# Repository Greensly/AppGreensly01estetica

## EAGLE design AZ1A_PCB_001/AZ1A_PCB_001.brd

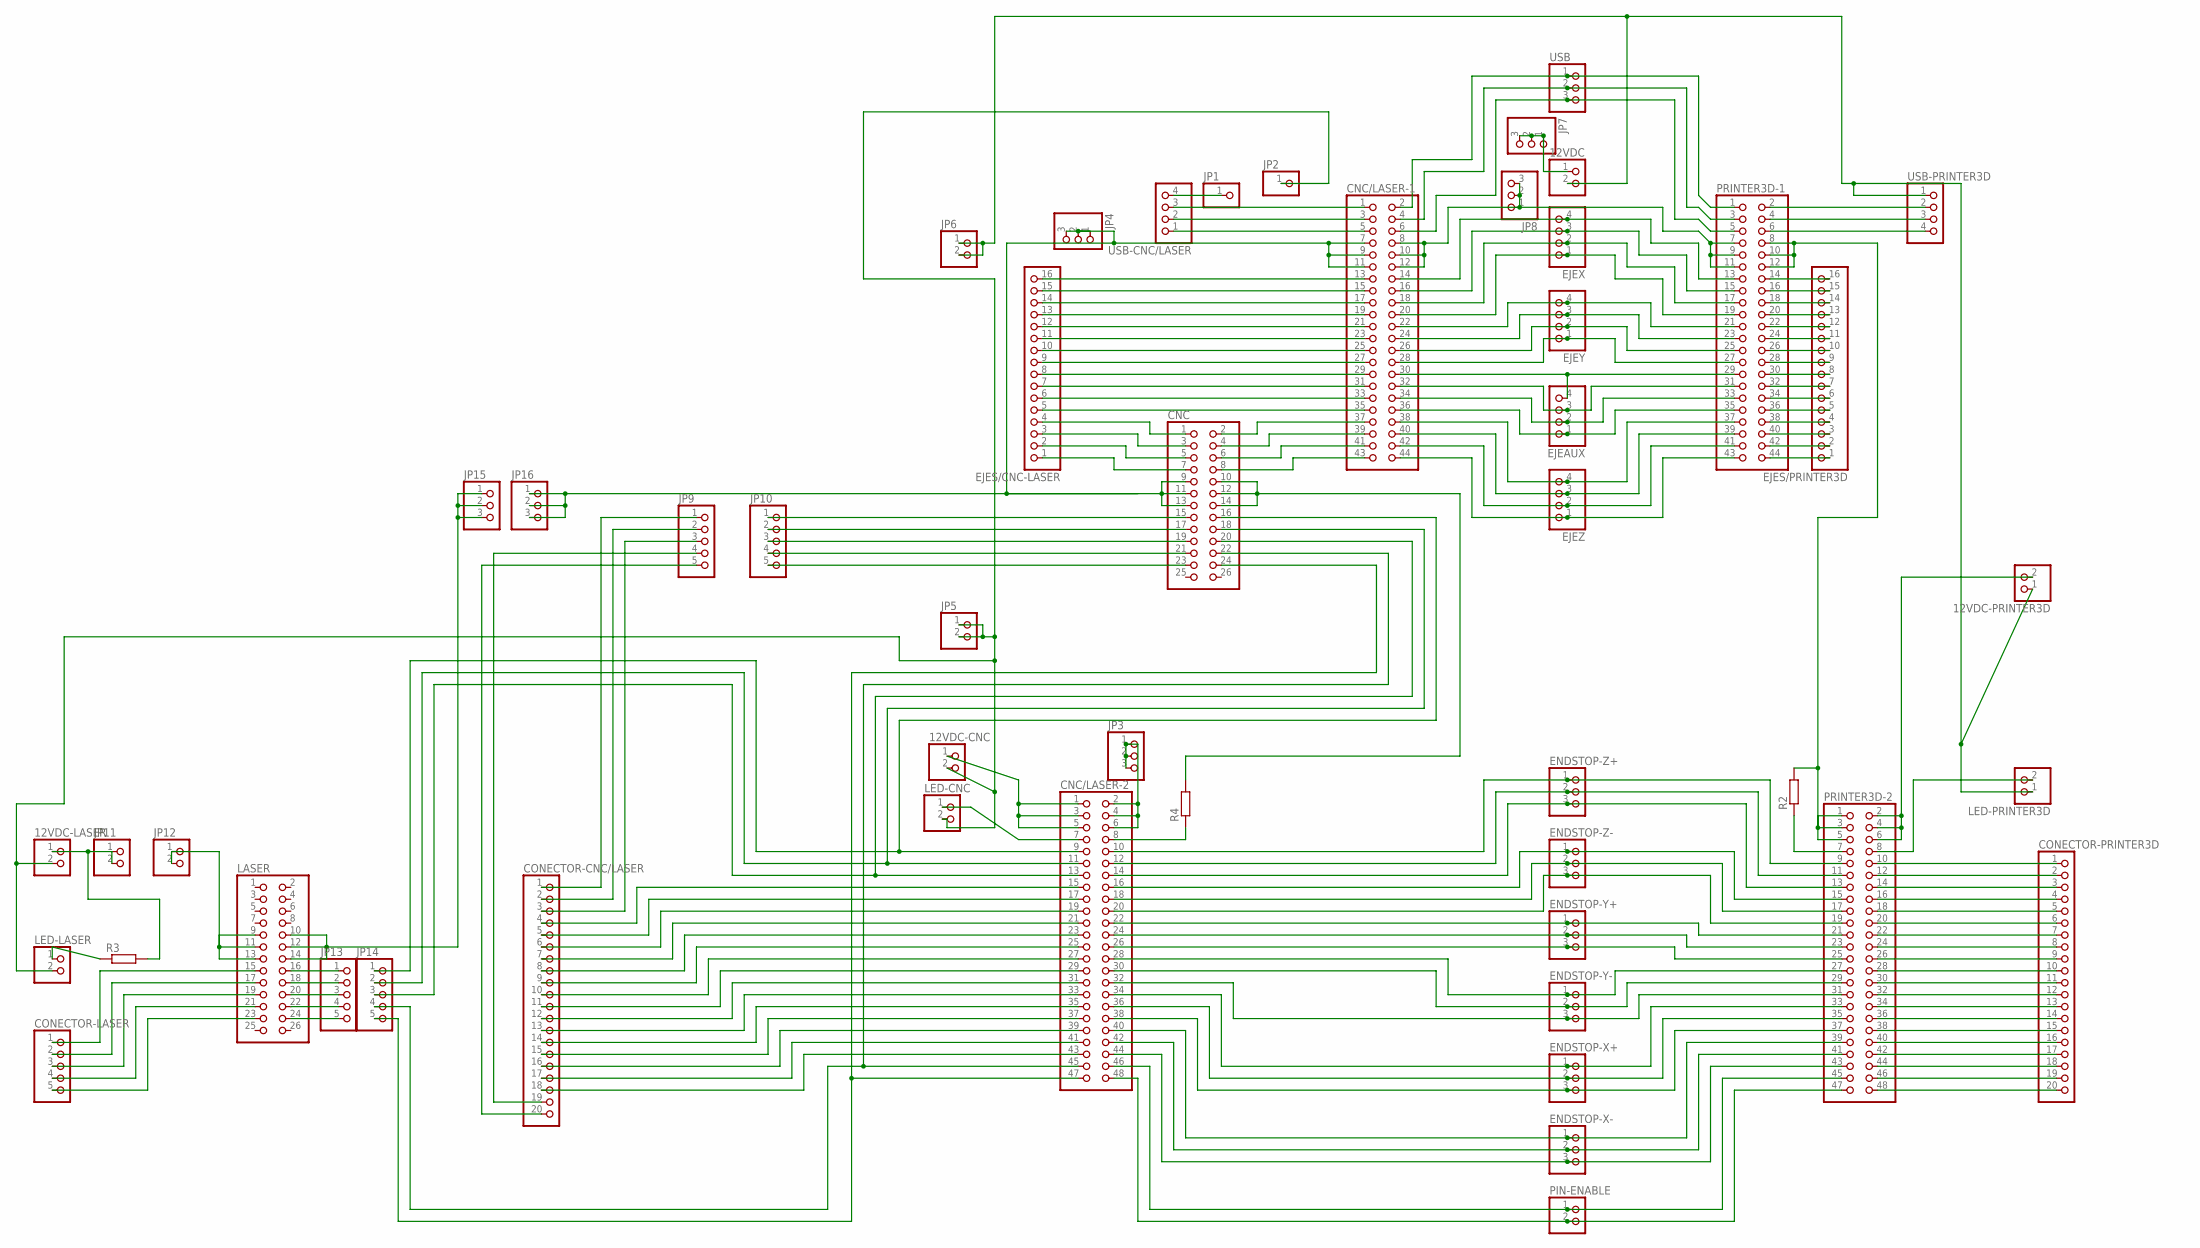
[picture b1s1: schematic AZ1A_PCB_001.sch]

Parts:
12VDC, 12VDC-CNC, 12VDC-LASER, 12VDC-PRINTER3D: PINHD-1X2; 1X02
CNC: PINHD-2X13; 2X13
CNC/LASER-1: PINHD-2X22; 2X22
CNC/LASER-2: PINHD-2X24; 2X24
CONECTOR-CNC/LASER: PINHD-1X20; 1X20
CONECTOR-LASER: PINHD-1X5; 1X05
CONECTOR-PRINTER3D: PINHD-1X20; 1X20
EJEAUX: PINHD-1X4; 1X04
EJES/CNC-LASER: PINHD-1X16; 1X16
EJES/PRINTER3D: PINHD-1X16; 1X16
EJEX: PINHD-1X4; 1X04
EJEY: PINHD-1X4; 1X04
EJEZ: PINHD-1X4; 1X04
ENDSTOP-X+: PINHD-1X3; 1X03
ENDSTOP-X-: PINHD-1X3; 1X03
ENDSTOP-Y+: PINHD-1X3; 1X03
ENDSTOP-Y-: PINHD-1X3; 1X03
ENDSTOP-Z+: PINHD-1X3; 1X03
ENDSTOP-Z-: PINHD-1X3; 1X03
JP1, JP2: PINHD-1X1; 1X01
JP3, JP4, JP7, JP8, JP15, JP16: PINHD-1X3; 1X03
JP5, JP6, JP11, JP12: PINHD-1X2; 1X02
JP9, JP10, JP13, JP14: PINHD-1X5; 1X05
LASER: PINHD-2X13; 2X13
LED-CNC: PINHD-1X2; 1X02
LED-LASER: PINHD-1X2; 1X02
LED-PRINTER3D: PINHD-1X2; 1X02
PIN-ENABLE: PINHD-1X2; 1X02
PRINTER3D-1: PINHD-2X22; 2X22
PRINTER3D-2: PINHD-2X24; 2X24
R2, R3, R4: R-EU_0204/5; 0204/5
USB: PINHD-1X3; 1X03
USB-CNC/LASER: PINHD-1X4; 1X04
USB-PRINTER3D: PINHD-1X4; 1X04

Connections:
unnamed: EJES/PRINTER3D.1, PRINTER3D-1.44
unnamed: CNC/LASER-1.16, EJEX.3, PRINTER3D-1.15
unnamed: CNC/LASER-1.18, EJEX.2, PRINTER3D-1.17
unnamed: CNC/LASER-1.20, EJEX.1, PRINTER3D-1.19
unnamed: CNC/LASER-1.22, EJEY.4, PRINTER3D-1.21
unnamed: CNC/LASER-1.24, EJEY.3, PRINTER3D-1.23
unnamed: CNC/LASER-1.26, EJEY.2, PRINTER3D-1.25
unnamed: CNC/LASER-1.28, EJEY.1, PRINTER3D-1.27
unnamed: CNC/LASER-1.30, EJEAUX.4, PRINTER3D-1.29
unnamed: CNC/LASER-1.32, EJEAUX.3, PRINTER3D-1.31
unnamed: CNC/LASER-1.34, EJEAUX.2, PRINTER3D-1.33
unnamed: CNC/LASER-1.36, EJEAUX.1, PRINTER3D-1.35
unnamed: CNC/LASER-1.38, EJEZ.4, PRINTER3D-1.37
unnamed: CNC/LASER-1.40, EJEZ.3, PRINTER3D-1.39
unnamed: CNC/LASER-1.42, EJEZ.2, PRINTER3D-1.41
unnamed: CNC/LASER-1.44, EJEZ.1, PRINTER3D-1.43
unnamed: CNC/LASER-1.8, CNC/LASER-1.10, CNC/LASER-1.12, JP8.1, JP8.2, JP8.3, PRINTER3D-1.7, PRINTER3D-1.9, PRINTER3D-1.11
unnamed: CNC.10, CNC.12, CNC.14, R4.2
unnamed: 12VDC-CNC.1, CNC/LASER-2.1, CNC/LASER-2.3, CNC/LASER-2.5
unnamed: CNC.1, EJES/CNC-LASER.4
unnamed: CNC/LASER-2.8, R4.1
unnamed: CNC/LASER-2.38, ENDSTOP-X+.3, PRINTER3D-2.37
unnamed: CNC.3, EJES/CNC-LASER.3
unnamed: CNC/LASER-2.36, ENDSTOP-X+.2, PRINTER3D-2.35
unnamed: CNC/LASER-2.34, ENDSTOP-X+.1, PRINTER3D-2.33
unnamed: CNC/LASER-2.32, ENDSTOP-Y-.3, PRINTER3D-2.31
unnamed: CNC/LASER-2.30, ENDSTOP-Y-.2, PRINTER3D-2.29
unnamed: CNC/LASER-2.28, ENDSTOP-Y-.1, PRINTER3D-2.27
unnamed: CNC/LASER-2.26, ENDSTOP-Y+.3, PRINTER3D-2.25
unnamed: CNC/LASER-2.24, ENDSTOP-Y+.2, PRINTER3D-2.23
unnamed: CNC/LASER-2.22, ENDSTOP-Y+.1, PRINTER3D-2.21
unnamed: CNC/LASER-2.20, ENDSTOP-Z-.3, PRINTER3D-2.19
unnamed: CNC/LASER-2.18, ENDSTOP-Z-.2, PRINTER3D-2.17
unnamed: CNC/LASER-2.16, ENDSTOP-Z-.1, PRINTER3D-2.15
unnamed: CNC/LASER-2.14, ENDSTOP-Z+.3, PRINTER3D-2.13
unnamed: CNC/LASER-2.12, ENDSTOP-Z+.2, PRINTER3D-2.11
unnamed: CNC/LASER-2.10, ENDSTOP-Z+.1, PRINTER3D-2.9
unnamed: CNC/LASER-2.40, ENDSTOP-X-.1, PRINTER3D-2.39
unnamed: CNC/LASER-2.48, PIN-ENABLE.2, PRINTER3D-2.47
unnamed: CNC/LASER-2.46, PIN-ENABLE.1, PRINTER3D-2.45
unnamed: CNC/LASER-2.44, ENDSTOP-X-.3, PRINTER3D-2.43
unnamed: CNC/LASER-2.42, ENDSTOP-X-.2, PRINTER3D-2.41
unnamed: CNC/LASER-2.7, LED-CNC.1
unnamed: CNC.5, EJES/CNC-LASER.2
unnamed: CNC.7, EJES/CNC-LASER.1
unnamed: CNC/LASER-1.35, EJES/CNC-LASER.5
unnamed: CNC/LASER-1.33, EJES/CNC-LASER.6
unnamed: CNC/LASER-1.31, EJES/CNC-LASER.7
unnamed: CNC/LASER-1.29, EJES/CNC-LASER.8
unnamed: CNC/LASER-1.27, EJES/CNC-LASER.9
unnamed: CNC/LASER-1.25, EJES/CNC-LASER.10
unnamed: CNC/LASER-1.23, EJES/CNC-LASER.11
unnamed: CNC/LASER-1.21, EJES/CNC-LASER.12
unnamed: CNC/LASER-1.15, EJES/CNC-LASER.15
unnamed: CNC/LASER-1.17, EJES/CNC-LASER.14
unnamed: CNC/LASER-1.19, EJES/CNC-LASER.13
unnamed: CNC/LASER-1.13, EJES/CNC-LASER.16
unnamed: CNC/LASER-1.14, EJEX.4, PRINTER3D-1.13
unnamed: EJES/PRINTER3D.2, PRINTER3D-1.42
unnamed: EJES/PRINTER3D.3, PRINTER3D-1.40
unnamed: EJES/PRINTER3D.4, PRINTER3D-1.38
unnamed: EJES/PRINTER3D.5, PRINTER3D-1.36
unnamed: EJES/PRINTER3D.6, PRINTER3D-1.34
unnamed: EJES/PRINTER3D.7, PRINTER3D-1.32
unnamed: EJES/PRINTER3D.8, PRINTER3D-1.30
unnamed: EJES/PRINTER3D.9, PRINTER3D-1.28
unnamed: EJES/PRINTER3D.10, PRINTER3D-1.26
unnamed: EJES/PRINTER3D.11, PRINTER3D-1.24
unnamed: EJES/PRINTER3D.12, PRINTER3D-1.22
unnamed: EJES/PRINTER3D.13, PRINTER3D-1.20
unnamed: EJES/PRINTER3D.14, PRINTER3D-1.18
unnamed: EJES/PRINTER3D.15, PRINTER3D-1.16
unnamed: EJES/PRINTER3D.16, PRINTER3D-1.14
unnamed: 12VDC-PRINTER3D.2, PRINTER3D-2.2, PRINTER3D-2.4, PRINTER3D-2.6
unnamed: PRINTER3D-1.8, PRINTER3D-1.10, PRINTER3D-1.12, PRINTER3D-2.1, PRINTER3D-2.3, PRINTER3D-2.5, R2.2
unnamed: PRINTER3D-2.7, R2.1
unnamed: LED-PRINTER3D.2, PRINTER3D-2.8
unnamed: CNC.2, CNC/LASER-1.37
unnamed: CNC.4, CNC/LASER-1.39
unnamed: CNC.6, CNC/LASER-1.41
unnamed: CNC.8, CNC/LASER-1.43
unnamed: CNC.16, CNC/LASER-2.9, JP14.1
unnamed: CNC.18, JP14.2
unnamed: CNC.20, CNC/LASER-2.13, JP14.3
unnamed: CNC.22, CNC/LASER-2.45, JP14.4
unnamed: CNC.24, CNC/LASER-2.47, JP14.5
unnamed: CONECTOR-CNC/LASER.1, JP9.1
unnamed: CONECTOR-CNC/LASER.2, JP9.2
unnamed: CONECTOR-CNC/LASER.3, JP9.3
unnamed: CNC/LASER-2.15, CONECTOR-CNC/LASER.4
unnamed: CNC/LASER-2.17, CONECTOR-CNC/LASER.5
unnamed: CNC/LASER-2.19, CONECTOR-CNC/LASER.6
unnamed: CNC/LASER-2.21, CONECTOR-CNC/LASER.7
unnamed: CNC/LASER-2.23, CONECTOR-CNC/LASER.8
unnamed: CNC/LASER-2.25, CONECTOR-CNC/LASER.9
unnamed: CNC/LASER-2.27, CONECTOR-CNC/LASER.10
unnamed: CNC/LASER-2.29, CONECTOR-CNC/LASER.11
unnamed: CNC/LASER-2.31, CONECTOR-CNC/LASER.12
unnamed: CNC/LASER-2.33, CONECTOR-CNC/LASER.13
unnamed: CNC/LASER-2.35, CONECTOR-CNC/LASER.14
unnamed: CNC/LASER-2.37, CONECTOR-CNC/LASER.15
unnamed: CNC/LASER-2.39, CONECTOR-CNC/LASER.16
unnamed: CNC/LASER-2.41, CONECTOR-CNC/LASER.17
unnamed: CNC/LASER-2.43, CONECTOR-CNC/LASER.18
unnamed: CONECTOR-CNC/LASER.19, JP9.4
unnamed: CONECTOR-CNC/LASER.20, JP9.5
unnamed: JP12.1, JP12.2, LASER.9, LASER.11, LASER.13
unnamed: LED-LASER.1, R3.1
unnamed: 12VDC-CNC.2, 12VDC-LASER.2, JP2.1, JP5.1, JP5.2, LED-CNC.2, LED-LASER.2
unnamed: CNC/LASER-1.6, PRINTER3D-1.5, USB.3
unnamed: CNC/LASER-1.4, PRINTER3D-1.3, USB.2
unnamed: CNC/LASER-1.2, PRINTER3D-1.1, USB.1
unnamed: CNC/LASER-1.5, USB-CNC/LASER.1
unnamed: CNC/LASER-1.3, USB-CNC/LASER.2
unnamed: CNC/LASER-1.1, USB-CNC/LASER.3
unnamed: PRINTER3D-1.6, USB-PRINTER3D.4
unnamed: PRINTER3D-1.4, USB-PRINTER3D.3
unnamed: PRINTER3D-1.2, USB-PRINTER3D.2
unnamed: CONECTOR-LASER.1, LASER.15
unnamed: CONECTOR-LASER.2, LASER.17
unnamed: CNC.9, CNC.11, CNC.13, CNC/LASER-1.7, CNC/LASER-1.9, CNC/LASER-1.11, JP4.1, JP4.2, JP4.3, JP16.1, JP16.2, JP16.3
unnamed: CONECTOR-LASER.3, LASER.19
unnamed: CONECTOR-LASER.4, LASER.21
unnamed: CONECTOR-LASER.5, LASER.23
unnamed: CONECTOR-PRINTER3D.1, PRINTER3D-2.10
unnamed: CONECTOR-PRINTER3D.2, PRINTER3D-2.12
unnamed: CONECTOR-PRINTER3D.3, PRINTER3D-2.14
unnamed: CONECTOR-PRINTER3D.4, PRINTER3D-2.16
unnamed: CONECTOR-PRINTER3D.5, PRINTER3D-2.18
unnamed: CONECTOR-PRINTER3D.6, PRINTER3D-2.20
unnamed: CONECTOR-PRINTER3D.7, PRINTER3D-2.22
unnamed: CONECTOR-PRINTER3D.8, PRINTER3D-2.24
unnamed: CONECTOR-PRINTER3D.9, PRINTER3D-2.26
unnamed: CONECTOR-PRINTER3D.10, PRINTER3D-2.28
unnamed: CONECTOR-PRINTER3D.11, PRINTER3D-2.30
unnamed: CONECTOR-PRINTER3D.12, PRINTER3D-2.32
unnamed: CONECTOR-PRINTER3D.13, PRINTER3D-2.34
unnamed: CONECTOR-PRINTER3D.14, PRINTER3D-2.36
unnamed: CONECTOR-PRINTER3D.15, PRINTER3D-2.38
unnamed: CONECTOR-PRINTER3D.16, PRINTER3D-2.40
unnamed: CONECTOR-PRINTER3D.17, PRINTER3D-2.42
unnamed: CONECTOR-PRINTER3D.18, PRINTER3D-2.44
unnamed: CONECTOR-PRINTER3D.19, PRINTER3D-2.46
unnamed: CONECTOR-PRINTER3D.20, PRINTER3D-2.48
unnamed: JP1.1, USB-CNC/LASER.4
unnamed: CNC/LASER-2.2, CNC/LASER-2.4, CNC/LASER-2.6, JP3.1, JP3.2, JP3.3
unnamed: CNC.15, JP10.1
unnamed: 12VDC.2, 12VDC-PRINTER3D.1, JP6.1, JP6.2, LED-PRINTER3D.1, USB-PRINTER3D.1
unnamed: 12VDC.1, JP7.1, JP7.2, JP7.3
unnamed: CNC.17, JP10.2
unnamed: CNC.19, JP10.3
unnamed: CNC.21, JP10.4
unnamed: CNC.23, JP10.5
unnamed: 12VDC-LASER.1, JP11.1, JP11.2, R3.2
unnamed: JP13.1, LASER.16
unnamed: JP13.2, LASER.18
unnamed: JP13.3, LASER.20
unnamed: JP13.4, LASER.22
unnamed: JP13.5, LASER.24
unnamed: JP15.1, JP15.2, JP15.3, LASER.10, LASER.12, LASER.14

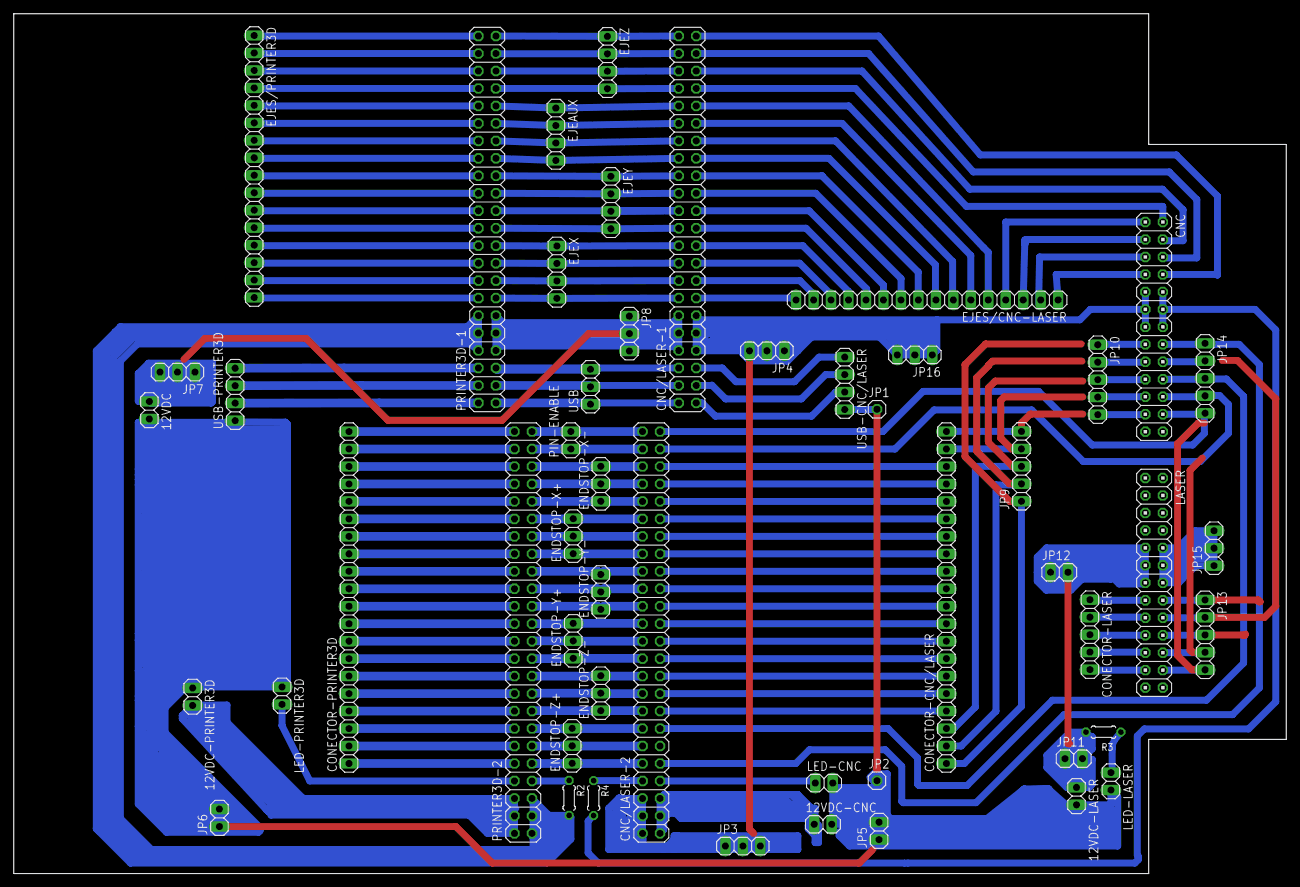
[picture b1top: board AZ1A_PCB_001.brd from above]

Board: 2 copper layers, 185.0 x 125.0 mm, 51 parts (0 on the bottom side), 160 nets.

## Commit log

2019-05-07 Archivo Git tips
2019-05-29 Agregue carpeta AZ1A_PCB con archivos
2019-05-30 Actualización de PCB
2019-05-31 Actualización PCB casi finalizando la PCB
2019-05-31 agregar tips para modificar archivos o programas en github
2019-06-01 Actualizacion de PCB y dimensiones de Arduino UNO y MEGA
2019-06-28 Se agregó carpeta Python Exercise
2019-07-01 se agregaron dos archivos python
